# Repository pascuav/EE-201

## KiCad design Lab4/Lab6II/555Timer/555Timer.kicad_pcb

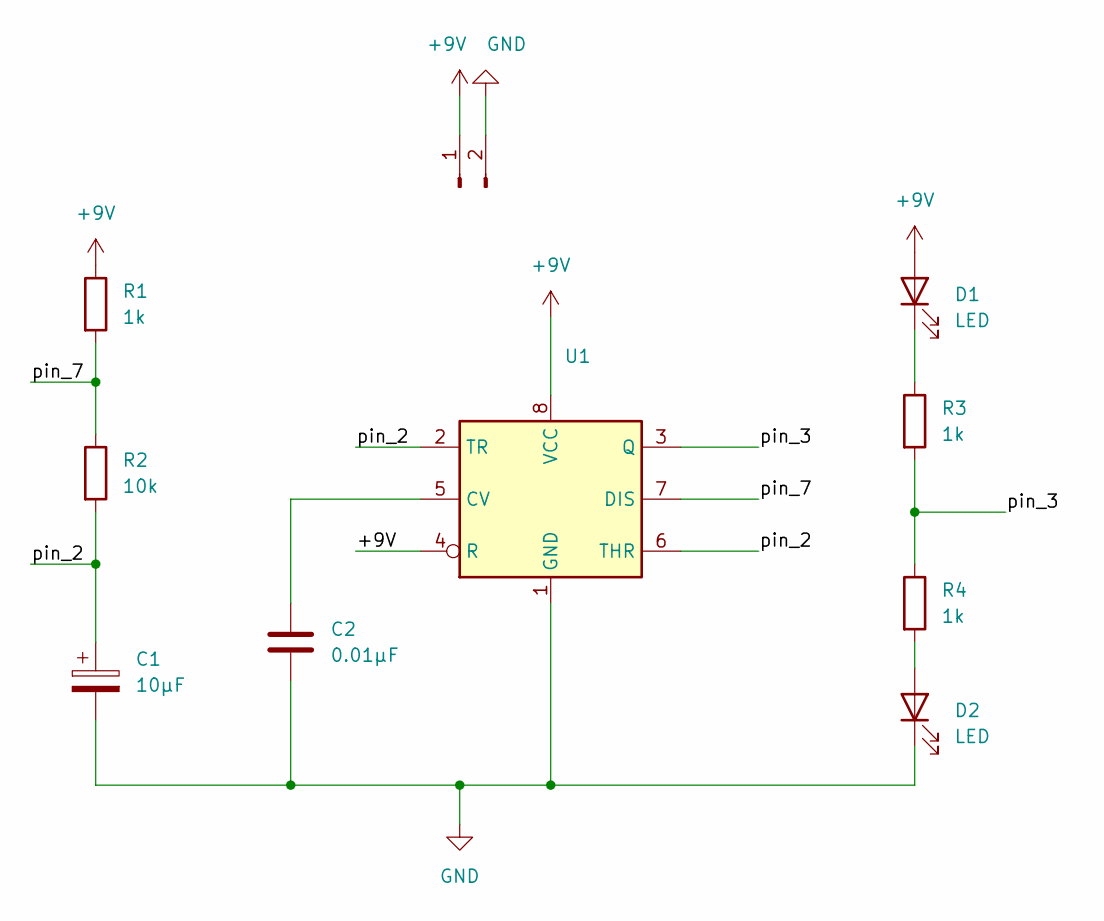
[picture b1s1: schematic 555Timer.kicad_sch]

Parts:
+9V1: Conn_01x02_Male; TerminalBlock_bornier-2_P5.08mm
C1: 10µF; CP_EIA-3216-18_Kemet-A_Pad1.58x1.35mm_HandSolder
C2: 0.01µF; C_0805_2012Metric_Pad1.18x1.45mm_HandSolder
D1, D2: LED; LED_1206_3216Metric_Pad1.42x1.75mm_HandSolder
R1, R3, R4: 1k; R_0805_2012Metric_Pad1.20x1.40mm_HandSolder
R2: 10k; R_0805_2012Metric_Pad1.20x1.40mm_HandSolder
U1: U1; SOIC-8-1EP_3.9x4.9mm_P1.27mm_EP2.29x3mm

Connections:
+9V: +9V1.1, D1.2 (A), R1.1, U1.4 (R), U1.8 (VCC)
/pin_2: C1.1, R2.2, U1.2 (TR), U1.6 (THR)
/pin_3: R3.2, R4.1, U1.3 (Q)
/pin_7: R1.2, R2.1, U1.7 (DIS)
GND: +9V1.2, C1.2, C2.2, D2.1 (K), U1.1 (GND)
unnamed: C2.1, U1.5 (CV)
unnamed: D1.1 (K), R3.1
unnamed: D2.2 (A), R4.2

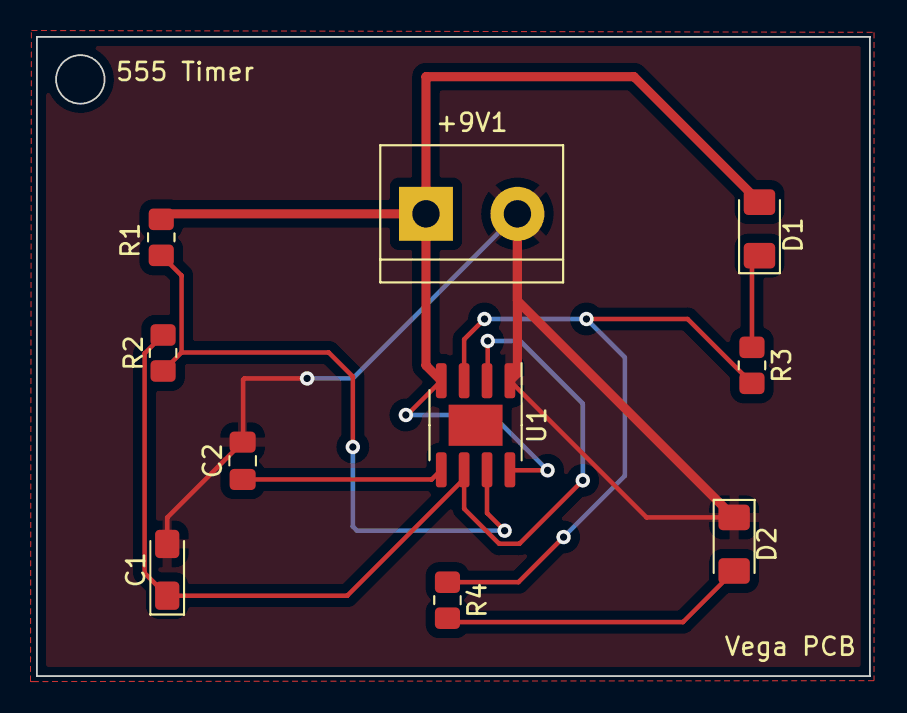
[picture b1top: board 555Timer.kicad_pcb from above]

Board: 2 copper layers, 46.3 x 35.5 mm, 10 parts (0 on the bottom side), 8 nets.

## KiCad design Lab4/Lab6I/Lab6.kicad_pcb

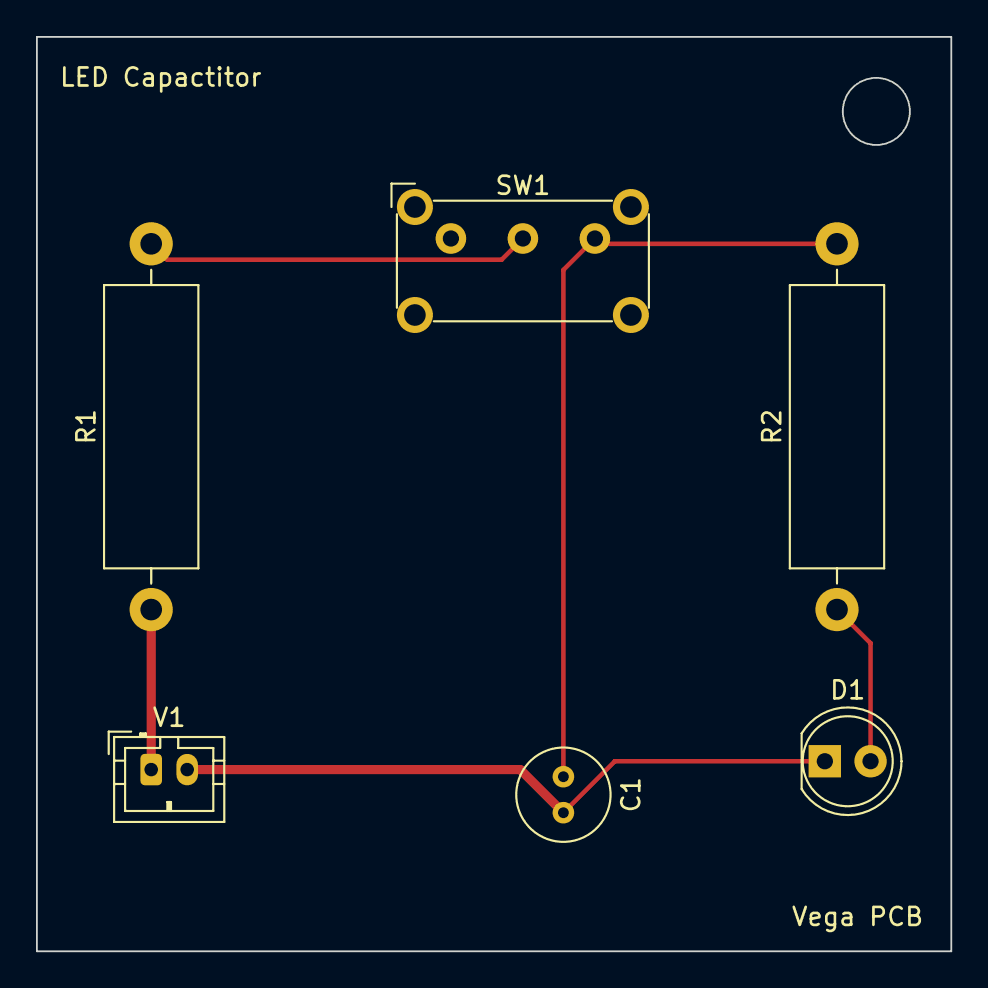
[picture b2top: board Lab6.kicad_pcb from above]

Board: 2 copper layers, 50.8 x 50.8 mm, 6 parts (0 on the bottom side), 5 nets.

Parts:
C1: 4.7 µF; C_Radial_D5.0mm_H5.0mm_P2.00mm
D1: LED; LED_D5.0mm
R1: 2.2 kΩ; R_Axial_DIN0516_L15.5mm_D5.0mm_P20.32mm_Horizontal
R2: 20 kΩ; R_Axial_DIN0516_L15.5mm_D5.0mm_P20.32mm_Horizontal
SW1: SW_SPDT; SW_E-Switch_EG1224_SPDT_Angled
V1: 9V; JST_PH_B2B-PH-K_1x02_P2.00mm_Vertical

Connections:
unnamed: C1.1, R2.2, SW1.3 (C)
unnamed: C1.2, D1.1 (K), V1.2
unnamed: D1.2 (A), R2.1
unnamed: R1.1, V1.1
unnamed: R1.2, SW1.2 (B)

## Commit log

2023-01-13 Commit #2
2023-01-13 Try #1
2023-01-13 added aboutme README
2023-01-20 initial commit 3
2023-01-27 Exercise #1
2023-01-27 ExerciseI & ExerciseII PDFs and KiCAD
2023-02-03 Soldering Practice
2023-02-03 Surface Soldering Practice
2023-02-10 Lab 6 PCB Designs
2023-02-10 Lab #6 Final
2023-02-18 Lab 7 Gerber and Drill Files
2023-03-11 Final PCB Images
